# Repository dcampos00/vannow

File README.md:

# VanNOW: Sistema de Relés Inalámbricos para Camper Van

Este proyecto (**VanNOW**) contiene el diseño de hardware (como código) y el firmware para un sistema de conmutación de relés y transistores inteligente en una camper van, controlado de forma inalámbrica por ESP32 mediante el protocolo autónomo ESP-NOW.

---

## Estructura del Repositorio

- **`docs/`**: Contiene la documentación del proyecto, decisiones de arquitectura y especificaciones eléctricas.
  - [propuesta_proyecto.md](docs/propuesta_proyecto.md): Propuesta inicial aprobada.
- **`firmware/`**: Código fuente C++ para los microcontroladores (gestión con PlatformIO).
  - **`central/`**: Firmware del receptor en el gabinete eléctrico central. Controla MOSFETs, PROFETs y optoacopladores.
    - [platformio.ini](firmware/central/platformio.ini)
    - [src/main.cpp](firmware/central/src/main.cpp)
  - **`remote/`**: Firmware para los paneles de pulsadores inalámbricos autónomos. Utiliza Deep Sleep profundo y envía comandos al central.
    - [platformio.ini](firmware/remote/platformio.ini)
    - [src/main.cpp](firmware/remote/src/main.cpp)
- **`hardware/`**: Código de diseño de circuito impreso (PCB) utilizando la plataforma de Hardware-as-Code **Atopile**.
  - **`central-pcb/`**:
    - [ato.yaml](hardware/central-pcb/ato.yaml)
    - [central.ato](hardware/central-pcb/central.ato): Esquema y conexiones de la placa central.

---

## Cómo Empezar

### 1. Firmware (PlatformIO)

Para cargar el software en tus módulos ESP32:

1. Abre la carpeta `firmware/central/` o `firmware/remote/` en VS Code con la extensión **PlatformIO** instalada.
2. En el módulo **Central**, compila y sube el código. Abre el monitor serial a `115200 baudios` y copia la **Dirección MAC** del dispositivo.
3. En el archivo [src/main.cpp del módulo remoto](firmware/remote/src/main.cpp#L17), reemplaza la dirección MAC en `centralMacAddress` con la dirección que copiaste del central:

   ```cpp
   uint8_t centralMacAddress[] = {0x12, 0x34, 0x56, 0x78, 0x9A, 0xBC};
   ```

4. Carga el código en el módulo remoto.
5. ¡Listo! Al presionar los pulsadores (conectados a los pines indicados), el remoto transmitirá la señal de conmutación al central.

### 2. Hardware (Atopile)

Para compilar el circuito y generar los archivos de KiCad:

1. Asegúrate de tener instalado Python y Atopile (`pip install atopile`).
2. Abre una terminal en `hardware/central-pcb/`.
3. Ejecuta el comando para compilar:

   ```bash
   ato build
   ```

4. Esto validará las conexiones eléctricas y generará los esquemáticos y la netlist en formato compatible con **KiCad**.

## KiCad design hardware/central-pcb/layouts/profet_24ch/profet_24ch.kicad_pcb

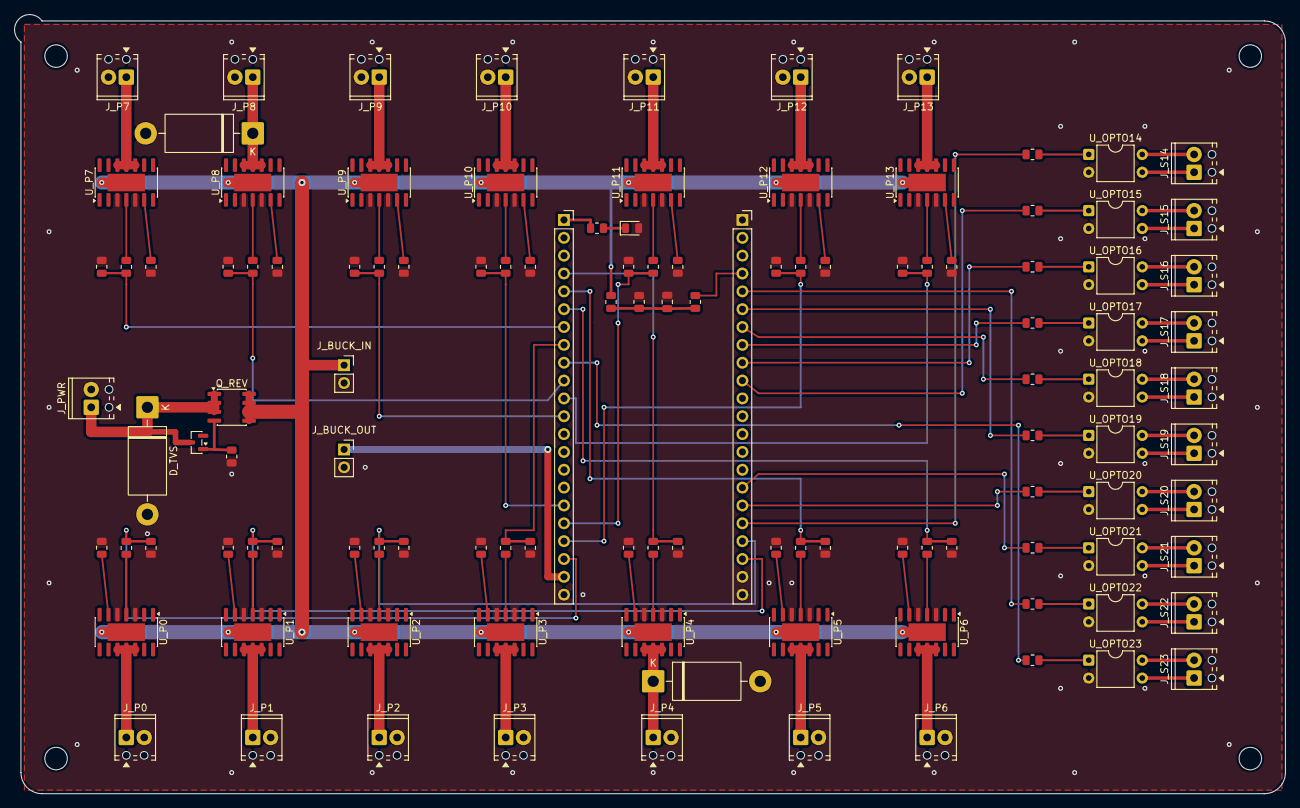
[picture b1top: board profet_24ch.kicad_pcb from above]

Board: 2 copper layers, 180.9 x 110.9 mm, 117 parts (0 on the bottom side), 105 nets.

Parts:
C_FILT: C_0805_2012Metric
D_FAN: D_DO-201AD_P15.24mm_Horizontal
D_PUMP: D_DO-201AD_P15.24mm_Horizontal
D_PWR: LED_0805_2012Metric
D_TVS: D_DO-201AD_P15.24mm_Horizontal
J_BUCK_IN: PinSocket_1x02_P2.54mm_Vertical
J_BUCK_OUT: PinSocket_1x02_P2.54mm_Vertical
J_MCU_L: PinSocket_1x22_P2.54mm_Vertical
J_MCU_R: PinSocket_1x22_P2.54mm_Vertical
J_P0, J_P1, J_P2, J_P3, J_P4, J_P5, J_P6, J_P7, J_P8, J_P9, J_P10, J_P11, J_P12, J_P13: TerminalBlock_Phoenix_MPT-0,5-2-2.54_1x02_P2.54mm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; TerminalBlock_Phoenix_MPT-0,5-2-2.54_1x02_P2.54mm_Horizontal
J_PWR: TerminalBlock_Phoenix_MPT-0,5-2-2.54_1x02_P2.54mm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; TerminalBlock_Phoenix_MPT-0,5-2-2.54_1x02_P2.54mm_Horizontal
J_S14, J_S15, J_S16, J_S17, J_S18, J_S19, J_S20, J_S21, J_S22, J_S23: TerminalBlock_Phoenix_MPT-0,5-2-2.54_1x02_P2.54mm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; TerminalBlock_Phoenix_MPT-0,5-2-2.54_1x02_P2.54mm_Horizontal
Q_REV: SOIC-8_3.9x4.9mm_P1.27mm
R_ADC: R_0805_2012Metric
R_CS0, R_CS1, R_CS2, R_CS3, R_CS4, R_CS5, R_CS6, R_CS7, R_CS8, R_CS9, R_CS10, R_CS11, R_CS12, R_CS13: R_0805_2012Metric
R_DIV_H: R_0805_2012Metric
R_DIV_L: R_0805_2012Metric
R_G0, R_G1, R_G2, R_G3, R_G4, R_G5, R_G6, R_G7, R_G8, R_G9, R_G10, R_G11, R_G12, R_G13: R_0805_2012Metric
R_OPTO14, R_OPTO15, R_OPTO16, R_OPTO17, R_OPTO18, R_OPTO19, R_OPTO20, R_OPTO21, R_OPTO22, R_OPTO23: R_0805_2012Metric
R_PD0, R_PD1, R_PD2, R_PD3, R_PD4, R_PD5, R_PD6, R_PD7, R_PD8, R_PD9, R_PD10, R_PD11, R_PD12, R_PD13: R_0805_2012Metric
R_PMOS: R_0805_2012Metric
R_PWR: R_0805_2012Metric
U_OPTO14, U_OPTO15, U_OPTO16, U_OPTO17, U_OPTO18, U_OPTO19, U_OPTO20, U_OPTO21, U_OPTO22, U_OPTO23: DIP-4_W7.62mm
U_P0, U_P1, U_P2, U_P3, U_P4, U_P5, U_P6, U_P7, U_P8, U_P9, U_P10, U_P11, U_P12, U_P13: SOIC-14-1EP_3.9x8.7mm_P1.27mm_EP4.3x4.7mm
Z_PMOS: SOT-23

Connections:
+3V3: J_MCU_L.1, R_PWR.1
+5V: J_BUCK_OUT.1, J_MCU_L.21
+12V: J_BUCK_IN.1, Q_REV.5, Q_REV.6, Q_REV.7, Q_REV.8, R_DIV_H.2, U_P0.15, U_P1.15, U_P2.15, U_P3.15, U_P4.15, U_P5.15, U_P6.15, U_P7.15, U_P8.15, U_P9.15, U_P10.15, U_P11.15, U_P12.15, U_P13.15
+12V_RAW: D_TVS.1, J_PWR.1, Q_REV.1, Q_REV.2, Q_REV.3, Z_PMOS.3
CH0_CTRL: J_MCU_L.20, R_G0.1, R_PD0.1
CH0_IN: R_G0.2, U_P0.4
CH0_IS: R_CS0.1, U_P0.6
CH0_OUT: J_P0.1, U_P0.10, U_P0.11, U_P0.12
CH1_CTRL: J_MCU_R.20, R_G1.1, R_PD1.1
CH1_IN: R_G1.2, U_P1.4
CH1_IS: R_CS1.1, U_P1.6
CH1_OUT: J_P1.1, U_P1.10, U_P1.11, U_P1.12
CH2_CTRL: J_MCU_R.19, R_G2.1, R_PD2.1
CH2_IN: R_G2.2, U_P2.4
CH2_IS: R_CS2.1, U_P2.6
CH2_OUT: J_P2.1, U_P2.10, U_P2.11, U_P2.12
CH3_CTRL: J_MCU_L.8, R_G3.1, R_PD3.1
CH3_IN: R_G3.2, U_P3.4
CH3_IS: R_CS3.1, U_P3.6
CH3_OUT: J_P3.1, U_P3.10, U_P3.11, U_P3.12
CH4_CTRL: J_MCU_L.4, R_G4.1, R_PD4.1
CH4_IN: R_G4.2, U_P4.4
CH4_IS: R_CS4.1, U_P4.6
CH4_OUT: D_PUMP.1, J_P4.1, U_P4.10, U_P4.11, U_P4.12
CH5_CTRL: J_MCU_L.5, R_G5.1, R_PD5.1
CH5_IN: R_G5.2, U_P5.4
CH5_IS: R_CS5.1, U_P5.6
CH5_OUT: J_P5.1, U_P5.10, U_P5.11, U_P5.12
CH6_CTRL: J_MCU_L.6, R_G6.1, R_PD6.1
CH6_IN: R_G6.2, U_P6.4
CH6_IS: R_CS6.1, U_P6.6
CH6_OUT: J_P6.1, U_P6.10, U_P6.11, U_P6.12
CH7_CTRL: J_MCU_L.7, R_G7.1, R_PD7.1
CH7_IN: R_G7.2, U_P7.4
CH7_IS: R_CS7.1, U_P7.6
CH7_OUT: J_P7.1, U_P7.10, U_P7.11, U_P7.12
CH8_CTRL: J_MCU_L.10, R_G8.1, R_PD8.1
CH8_IN: R_G8.2, U_P8.4
CH8_IS: R_CS8.1, U_P8.6
CH8_OUT: D_FAN.1, J_P8.1, U_P8.10, U_P8.11, U_P8.12
CH9_CTRL: J_MCU_L.12, R_G9.1, R_PD9.1
CH9_IN: R_G9.2, U_P9.4
CH9_IS: R_CS9.1, U_P9.6
CH9_OUT: J_P9.1, U_P9.10, U_P9.11, U_P9.12
CH10_CTRL: J_MCU_L.17, R_G10.1, R_PD10.1
CH10_IN: R_G10.2, U_P10.4
CH10_IS: R_CS10.1, U_P10.6
CH10_OUT: J_P10.1, U_P10.10, U_P10.11, U_P10.12
CH11_CTRL: J_MCU_L.18, R_G11.1, R_PD11.1
CH11_IN: R_G11.2, U_P11.4
CH11_IS: R_CS11.1, U_P11.6
CH11_OUT: J_P11.1, U_P11.10, U_P11.11, U_P11.12
CH12_CTRL: J_MCU_L.19, R_G12.1, R_PD12.1
CH12_IN: R_G12.2, U_P12.4
CH12_IS: R_CS12.1, U_P12.6
CH12_OUT: J_P12.1, U_P12.10, U_P12.11, U_P12.12
CH13_CTRL: J_MCU_L.11, R_G13.1, R_PD13.1
CH13_IN: R_G13.2, U_P13.4
CH13_IS: R_CS13.1, U_P13.6
CH13_OUT: J_P13.1, U_P13.10, U_P13.11, U_P13.12
CH14_ANODE: R_OPTO14.2, U_OPTO14.1
CH14_C: J_S14.2, U_OPTO14.4
CH14_CTRL: J_MCU_R.18, R_OPTO14.1
CH14_E: J_S14.1, U_OPTO14.3
CH15_ANODE: R_OPTO15.2, U_OPTO15.1
CH15_C: J_S15.2, U_OPTO15.4
CH15_CTRL: J_MCU_R.10, R_OPTO15.1
CH15_E: J_S15.1, U_OPTO15.3
CH16_ANODE: R_OPTO16.2, U_OPTO16.1
CH16_C: J_S16.2, U_OPTO16.4
CH16_CTRL: J_MCU_R.9, R_OPTO16.1
CH16_E: J_S16.1, U_OPTO16.3
CH17_ANODE: R_OPTO17.2, U_OPTO17.1
CH17_C: J_S17.2, U_OPTO17.4
CH17_CTRL: J_MCU_R.8, R_OPTO17.1
CH17_E: J_S17.1, U_OPTO17.3
CH18_ANODE: R_OPTO18.2, U_OPTO18.1
CH18_C: J_S18.2, U_OPTO18.4
CH18_CTRL: J_MCU_R.7, R_OPTO18.1
CH18_E: J_S18.1, U_OPTO18.3
CH19_ANODE: R_OPTO19.2, U_OPTO19.1
CH19_C: J_S19.2, U_OPTO19.4
CH19_CTRL: J_MCU_R.6, R_OPTO19.1
CH19_E: J_S19.1, U_OPTO19.3
CH20_ANODE: R_OPTO20.2, U_OPTO20.1
CH20_C: J_S20.2, U_OPTO20.4
CH20_CTRL: J_MCU_R.17, R_OPTO20.1
CH20_E: J_S20.1, U_OPTO20.3
CH21_ANODE: R_OPTO21.2, U_OPTO21.1
CH21_C: J_S21.2, U_OPTO21.4
CH21_CTRL: J_MCU_R.16, R_OPTO21.1
CH21_E: J_S21.1, U_OPTO21.3
CH22_ANODE: R_OPTO22.2, U_OPTO22.1
CH22_C: J_S22.2, U_OPTO22.4
CH22_CTRL: J_MCU_R.5, R_OPTO22.1
CH22_E: J_S22.1, U_OPTO22.3
CH23_ANODE: R_OPTO23.2, U_OPTO23.1
CH23_C: J_S23.2, U_OPTO23.4
CH23_CTRL: J_MCU_L.9, R_OPTO23.1
CH23_E: J_S23.1, U_OPTO23.3
GND: C_FILT.2, D_FAN.2, D_PUMP.2, D_PWR.2, D_TVS.2, J_BUCK_IN.2, J_BUCK_OUT.2, J_MCU_L.22, J_MCU_R.1, J_MCU_R.21, J_MCU_R.22, J_P0.2, J_P1.2, J_P2.2, J_P3.2, J_P4.2, J_P5.2, J_P6.2, J_P7.2, J_P8.2, J_P9.2, J_P10.2, J_P11.2, J_P12.2, J_P13.2, J_PWR.2, R_CS0.2, R_CS1.2, R_CS2.2, R_CS3.2, R_CS4.2, R_CS5.2, R_CS6.2, R_CS7.2, R_CS8.2, R_CS9.2, R_CS10.2, R_CS11.2, R_CS12.2, R_CS13.2, R_DIV_L.2, R_PD0.2, R_PD1.2, R_PD2.2, R_PD3.2, R_PD4.2, R_PD5.2, R_PD6.2, R_PD7.2, R_PD8.2, R_PD9.2, R_PD10.2, R_PD11.2, R_PD12.2, R_PD13.2, R_PMOS.1, U_OPTO14.2, U_OPTO15.2, U_OPTO16.2, U_OPTO17.2, U_OPTO18.2, U_OPTO19.2, U_OPTO20.2, U_OPTO21.2, U_OPTO22.2, U_OPTO23.2, U_P0.3, U_P0.5, U_P1.3, U_P1.5, U_P2.3, U_P2.5, U_P3.3, U_P3.5, U_P4.3, U_P4.5, U_P5.3, U_P5.5, U_P6.3, U_P6.5, U_P7.3, U_P7.5, U_P8.3, U_P8.5, U_P9.3, U_P9.5, U_P10.3, U_P10.5, U_P11.3, U_P11.5, U_P12.3, U_P12.5, U_P13.3, U_P13.5
LED_PWR_A: D_PWR.1, R_PWR.2
PMOS_GATE: Q_REV.4, R_PMOS.2, Z_PMOS.1
V_BAT_ADC: J_MCU_R.4, R_ADC.2
V_BAT_DIV: C_FILT.1, R_ADC.1, R_DIV_H.1, R_DIV_L.1

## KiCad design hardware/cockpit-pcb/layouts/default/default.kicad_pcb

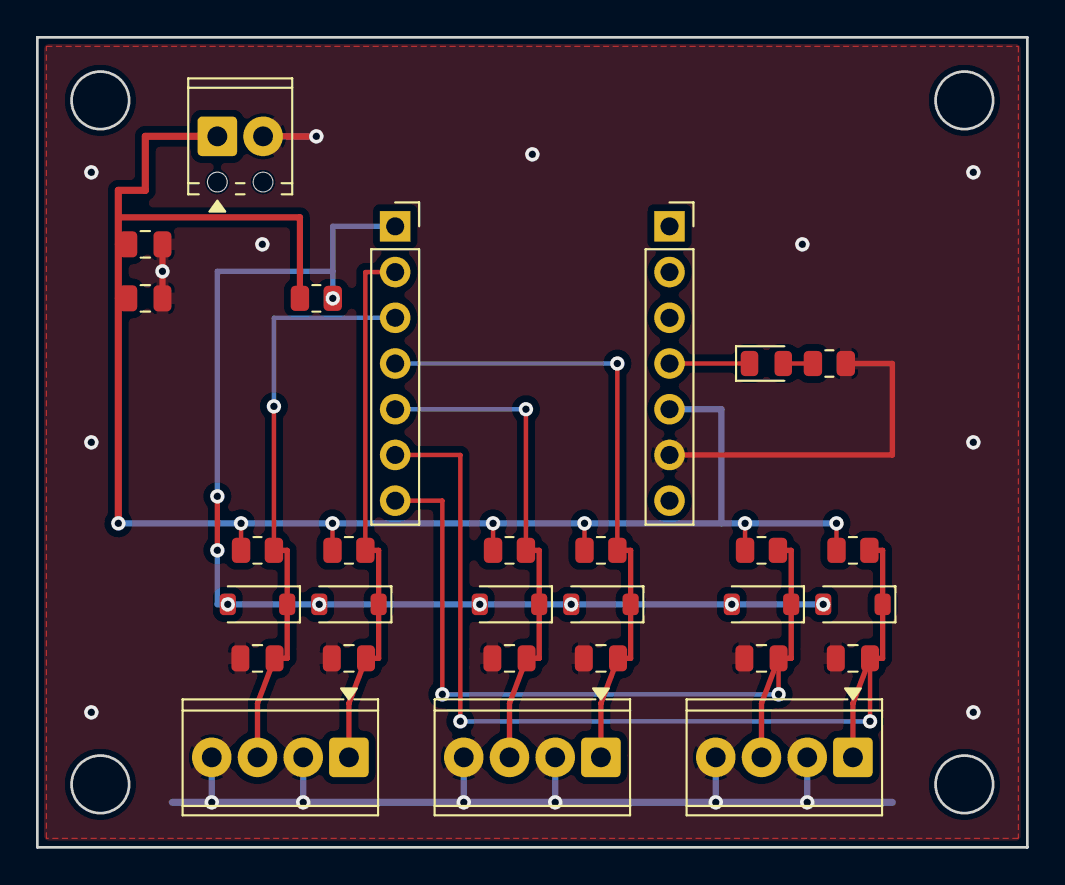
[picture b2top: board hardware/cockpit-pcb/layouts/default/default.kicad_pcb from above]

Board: 2 copper layers, 55.0 x 45.0 mm, 29 parts (0 on the bottom side), 11 nets.

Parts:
C1, C2, C3, C4, C5, C6, C7, C8: C_0805_2012Metric
D1, D2, D3, D4, D5, D6: D_SOD-123
D7: LED_0805_2012Metric
J1: TerminalBlock_Phoenix_MPT-0,5-2-2.54_1x02_P2.54mm_Horizontal
J2, J3: PinSocket_1x07_P2.54mm_Vertical
J4, J5, J6: TerminalBlock_Phoenix_MPT-0,5-4-2.54_1x04_P2.54mm_Horizontal
R1, R2, R3, R4, R5, R6, R7, R8: R_0805_2012Metric

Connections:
1: C3.1, D1.1, J2.2, J4.1, R1.2
1-1: C5.1, D3.1, J2.4, J5.1, R3.2
1-2: C7.1, D5.1, J2.6, J6.1, R5.2
anode: D7.1, J3.4
cathode: D7.2, R7.1
gnd: C1.2, C2.2, C3.2, C4.2, C5.2, C6.2, C7.2, C8.2, J1.2, J3.6, J4.2, J4.4, J5.2, J5.4, J6.2, J6.4, R7.2
mcu_sense: C4.1, D2.1, J2.3, J4.3, R2.2
mcu_sense-1: C6.1, D4.1, J2.5, J5.3, R4.2
mcu_sense-2: C8.1, D6.1, J2.7, J6.3, R6.2
vcc: C1.1, C2.1, J1.1, J3.5, R1.1, R2.1, R3.1, R4.1, R5.1, R6.1, R8.1
wakeup_bus: D1.2, D2.2, D3.2, D4.2, D5.2, D6.2, J2.1, R8.2

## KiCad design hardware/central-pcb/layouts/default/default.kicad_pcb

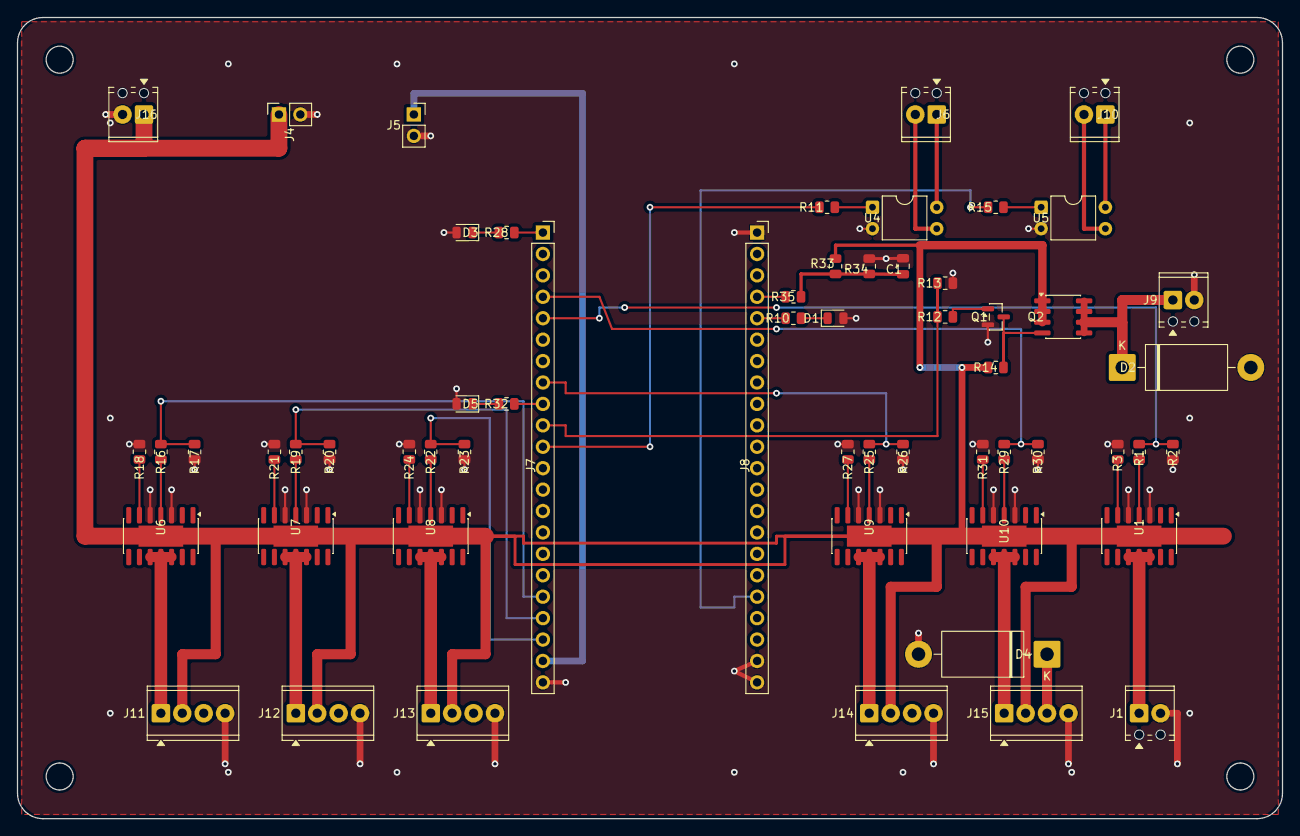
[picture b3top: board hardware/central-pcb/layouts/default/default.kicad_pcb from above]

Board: 2 copper layers, 150.0 x 95.0 mm, 59 parts (0 on the bottom side), 48 nets.

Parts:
C1: C_0805_2012Metric
D1, D3, D5: LED_0805_2012Metric
D2, D4: D_DO-201AD_P15.24mm_Horizontal
J1, J6, J9, J10, J16: TerminalBlock_Phoenix_MPT-0,5-2-2.54_1x02_P2.54mm_Horizontal
J4, J5: PinSocket_1x02_P2.54mm_Vertical
J7, J8: PinSocket_1x22_P2.54mm_Vertical
J11, J12, J13, J14, J15: TerminalBlock_Phoenix_MPT-0,5-4-2.54_1x04_P2.54mm_Horizontal
Q1: SOT-23
Q2: SOIC-8_3.9x4.9mm_P1.27mm
R1, R2, R3, R10, R11, R12, R13, R14, R15, R16, R17, R18, R19, R20, R21, R22, R23, R24, R25, R26, R27, R28, R29, R30, R31, R32, R33, R34, R35: R_0805_2012Metric
U1, U6, U7, U8, U9, U10: SOIC-14-1EP_3.9x8.7mm_P1.27mm_EP4.3x4.7mm
U4, U5: DIP-4_W7.62mm

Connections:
1: J8.5, R10.1
1-1: J7.9, R32.1
1-2: J7.1, R28.1
1-3: D2.1, J9.1, Q2.5, Q2.6, Q2.7, Q2.8
anode: D1.1, R10.2
anode-1: D3.1, R28.2
anode-2: D5.1, R32.2
cathode: D4.1, J15.3
control: J7.5, R1.1, R2.1
control-3: J7.11, R11.1
control-4: J7.18, R16.1, R17.1
control-5: J7.19, R19.1, R20.1
control-6: J7.20, R22.1, R23.1
control-7: J7.8, R25.1, R26.1
control-8: J7.10, R12.1, R13.1
control-9: J8.18, R15.1
control-10: J7.4, R29.1, R30.1
current_sense: R3.1, U1.6
dcdc_opto-anode: R11.2, U4.1
drain: Q1.3, Q2.4, R14.1
gate: Q1.1, R12.2
gnd: C1.2, D1.2, D2.2, D3.2, D4.2, D5.2, J1.2, J4.2, J5.2, J7.22, J8.1, J8.21, J8.22, J9.2, J11.4, J12.4, J13.4, J14.4, J15.4, J16.2, Q1.2, R2.2, R3.2, R13.2, R17.2, R18.2, R20.2, R21.2, R23.2, R24.2, R26.2, R27.2, R30.2, R31.2, R34.2, U1.3, U1.5, U4.2, U5.2, U6.3, U6.5, U7.3, U7.5, U8.3, U8.5, U9.3, U9.5, U10.3, U10.5
input: R1.2, U1.4
inverter_opto-anode: R15.2, U5.1
led_zone1_stage-current_sense: R18.1, U6.6
led_zone1_stage-input: R16.2, U6.4
led_zone2_stage-current_sense: R21.1, U7.6
led_zone2_stage-input: R19.2, U7.4
led_zone3_stage-current_sense: R24.1, U8.6
led_zone3_stage-input: R22.2, U8.4
led_zone4_stage-current_sense: R27.1, U9.6
led_zone4_stage-input: R25.2, U9.4
out_collector: J6.1, U4.4
out_collector-1: J10.1, U5.4
out_emitter: J6.2, U4.3
out_emitter-1: J10.2, U5.3
power_in: J4.1, J11.2, J12.2, J13.2, J14.2, J15.2, J16.1, Q2.1, Q2.2, Q2.3, R14.2, R33.1, U1.15, U6.15, U7.15, U8.15, U9.15, U10.15
power_out: J1.1, U1.10, U1.11, U1.12
power_out-3: J11.1, U6.10, U6.11, U6.12
power_out-4: J12.1, U7.10, U7.11, U7.12
power_out-5: J13.1, U8.10, U8.11, U8.12
power_out-6: J14.1, U9.10, U9.11, U9.12
power_out-7: J15.1, U10.10, U10.11, U10.12
pump_stage-current_sense: R31.1, U10.6
pump_stage-input: R29.2, U10.4
v_mcu_5v: J5.1, J7.21
v_out: J8.4, R35.2
voltage_sensor-1: C1.1, R33.2, R34.1, R35.1

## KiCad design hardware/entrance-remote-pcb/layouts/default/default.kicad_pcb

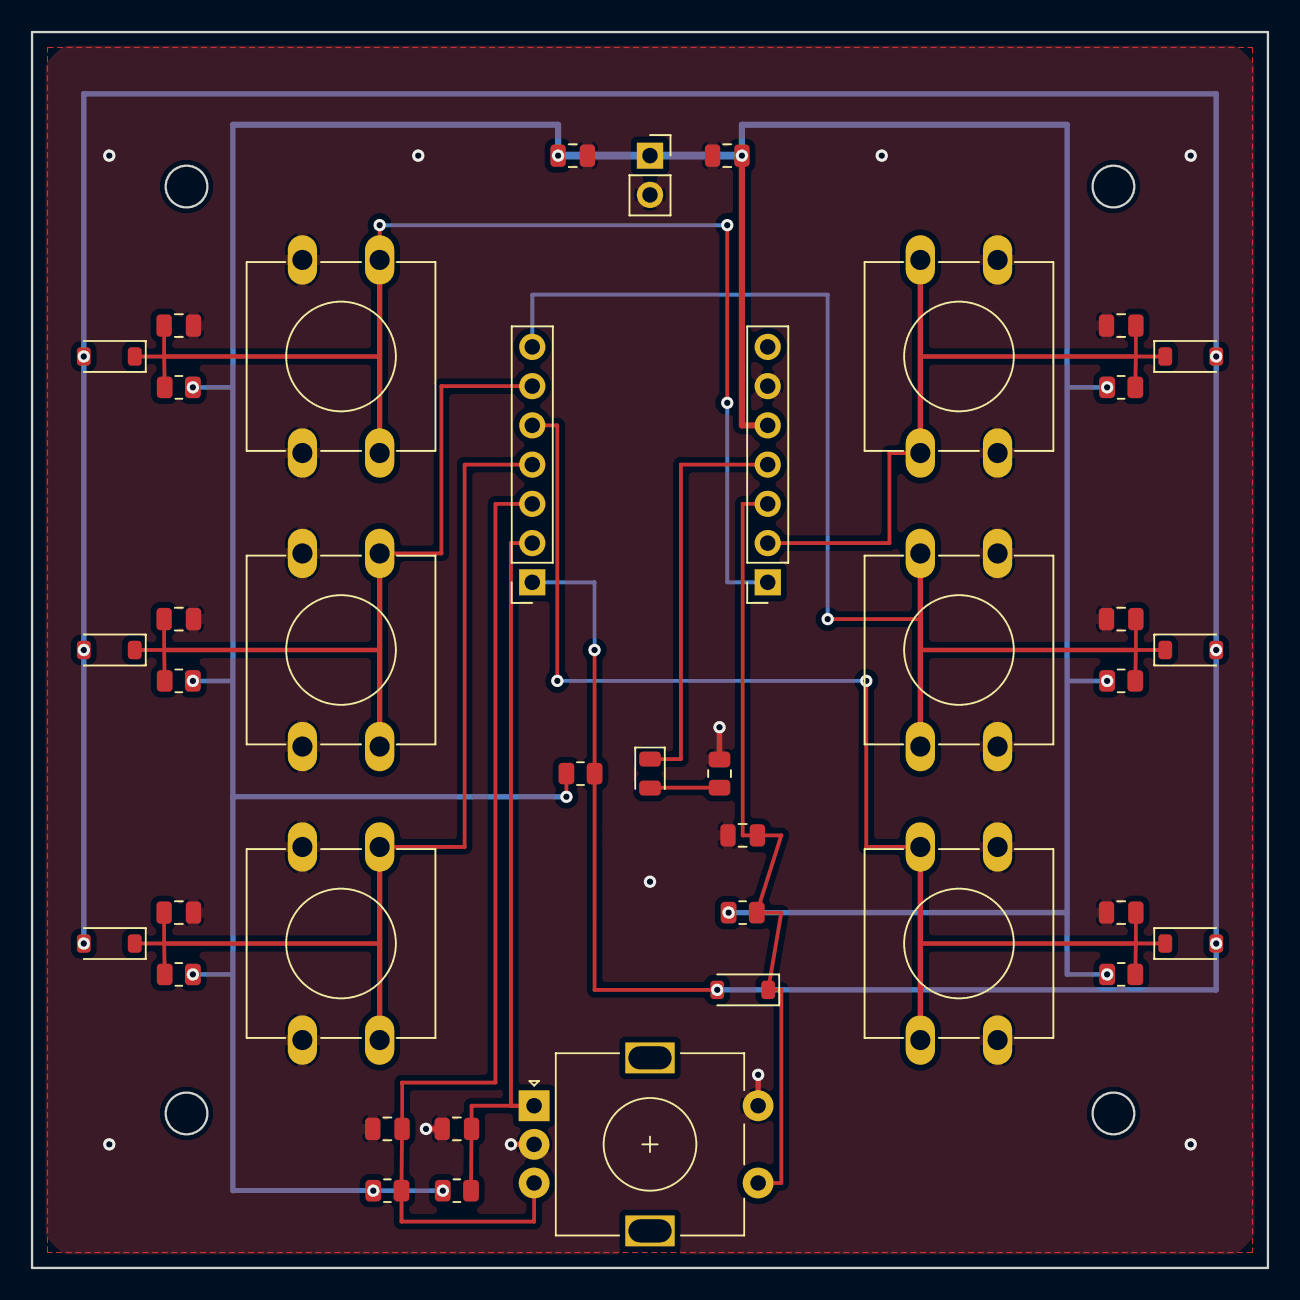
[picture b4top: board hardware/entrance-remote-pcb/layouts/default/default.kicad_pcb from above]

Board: 2 copper layers, 80.0 x 80.0 mm, 40 parts (0 on the bottom side), 14 nets.

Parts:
C1, C2, C3, C4, C5, C6, C7, C8, C9, C10, C11: C_0805_2012Metric
D1, D2, D3, D4, D5, D6, D7: D_SOD-123
D8: LED_0805_2012Metric
J1: PinSocket_1x02_P2.54mm_Vertical
J2, J3: PinSocket_1x07_P2.54mm_Vertical
R1, R2, R3, R4, R5, R6, R7, R8, R9, R10, R11: R_0805_2012Metric
SW1, SW2, SW3, SW4, SW5, SW6: SW_PUSH-12mm
SW7: RotaryEncoder_Alps_EC11E-Switch_Vertical_H20mm

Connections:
1: C1.1, D1.1, J3.2, R1.2, SW1.1
1-1: C2.1, D2.1, J3.1, R2.2, SW2.1
1-2: C3.1, D3.1, J2.4, R3.2, SW3.1
1-3: C4.1, D4.1, J2.5, R4.2, SW4.1
1-4: C5.1, D5.1, J2.6, R5.2, SW5.1
1-5: C6.1, D6.1, J2.7, R6.2, SW6.1
1-6: C11.1, D7.1, J3.3, R9.2, SW7.S1
2: C1.2, C2.2, C3.2, C4.2, C5.2, C6.2, C7.2, C8.2, C9.2, C10.2, C11.2, J1.2, J3.6, R10.2, SW1.2, SW2.2, SW3.2, SW4.2, SW5.2, SW6.2, SW7.C, SW7.S2
A: C9.1, J2.2, R7.2, SW7.A
B: C10.1, J2.3, R8.2, SW7.B
anode: D8.1, J3.4
cathode: D8.2, R10.1
vcc: C7.1, C8.1, J1.1, J3.5, R1.1, R2.1, R3.1, R4.1, R5.1, R6.1, R7.1, R8.1, R9.1, R11.1
wakeup_bus: D1.2, D2.2, D3.2, D4.2, D5.2, D6.2, D7.2, J2.1, R11.2

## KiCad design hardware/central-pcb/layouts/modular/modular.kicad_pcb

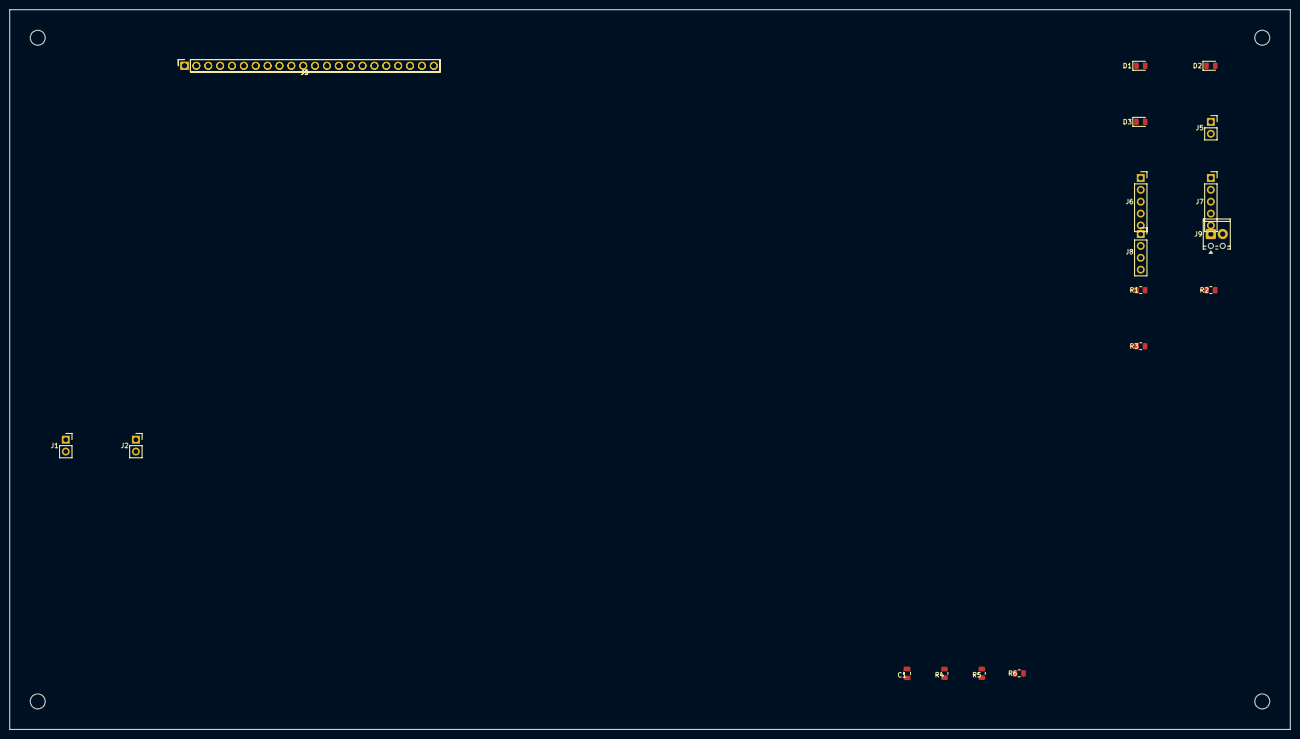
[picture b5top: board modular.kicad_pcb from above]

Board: 2 copper layers, 274.0 x 154.0 mm, 19 parts (0 on the bottom side), 22 nets, no tracks yet.

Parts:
C1: C_0805_2012Metric
D1, D2, D3: LED_0805_2012Metric
J1, J2, J5: PinSocket_1x02_P2.54mm_Vertical
J3, J4: PinSocket_1x22_P2.54mm_Vertical
J6, J7: PinSocket_1x05_P2.54mm_Vertical
J8: PinSocket_1x04_P2.54mm_Vertical
J9: TerminalBlock_Phoenix_MPT-0,5-2-2.54_1x02_P2.54mm_Horizontal
R1, R2, R3, R4, R5, R6: R_0805_2012Metric

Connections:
1: J4.5, R1.1
1-1: J3.9, R3.1
1-2: J3.1, R2.1
2: C1.2, D1.2, D2.2, D3.2, J1.2, J2.2, J3.22, J4.1, J4.21, J4.22, J5.1, J6.1, J7.1, J8.1, J9.2, R5.2
2-1: J3.18, J6.2
2-2: J4.18, J8.2
2-3: J3.4, J7.2
2-4: J3.7, J5.2
3: J3.19, J6.3
3-1: J3.10, J7.3
3-2: J3.11, J8.3
4: J3.20, J6.4
4-1: J3.5, J7.4
5: J3.8, J6.5
5-1: J3.6, J7.5
anode: D1.1, R1.2
anode-1: D2.1, R2.2
anode-2: D3.1, R3.2
v_bat_12v: J1.1, J9.1, R4.1
v_mcu_5v: J2.1, J3.21
v_out: J4.4, R6.2
voltage_sensor-1: C1.1, R4.2, R5.1, R6.1
